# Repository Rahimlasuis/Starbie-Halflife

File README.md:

<h1>Starbie</h1>
<h2>Description</h2>
This is my very first hardware project.
i followed the starbie guide on halflife.
building some kind of desktop companion with some personal additional functions
<h2>Some of the processes</h2>
i started by bringing in components , symbols and power symbols in the schematic.
then i wired them up according to the guide.
i updated the pcb
traced the edges
routed the pcb
run DHR
ignored the errors,
I already fixed all the errors after my first rejection on halflife lol.
added some components of my own
opened arduino ide
installed all the things i was askd to install by the guide.
pasted the code
edited the code to work with my components
troublshooted
cried
tears
compiling errors, so many times, i think due to repeated lines of the same code
it finally wokrked

google was my friend all the way.
and it also gave me lot of work.
never let AI write codes for you.

I also suffered a lot because of my system. It was so slow and at some point i lost unsaved changes. I cried lol

here are some images too

<h2>Final Image</h2>

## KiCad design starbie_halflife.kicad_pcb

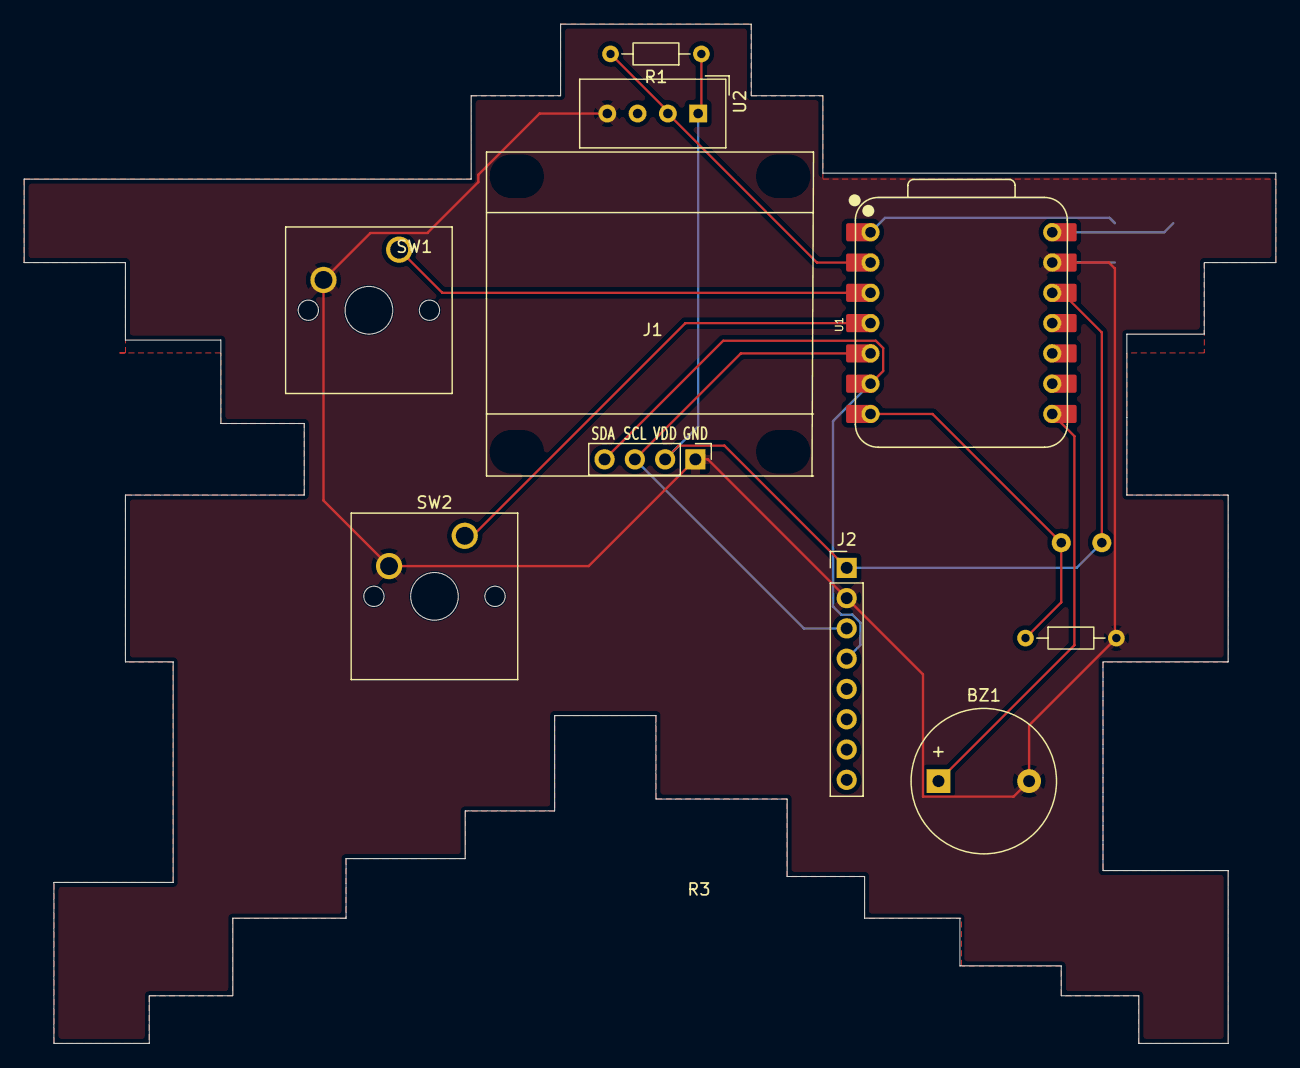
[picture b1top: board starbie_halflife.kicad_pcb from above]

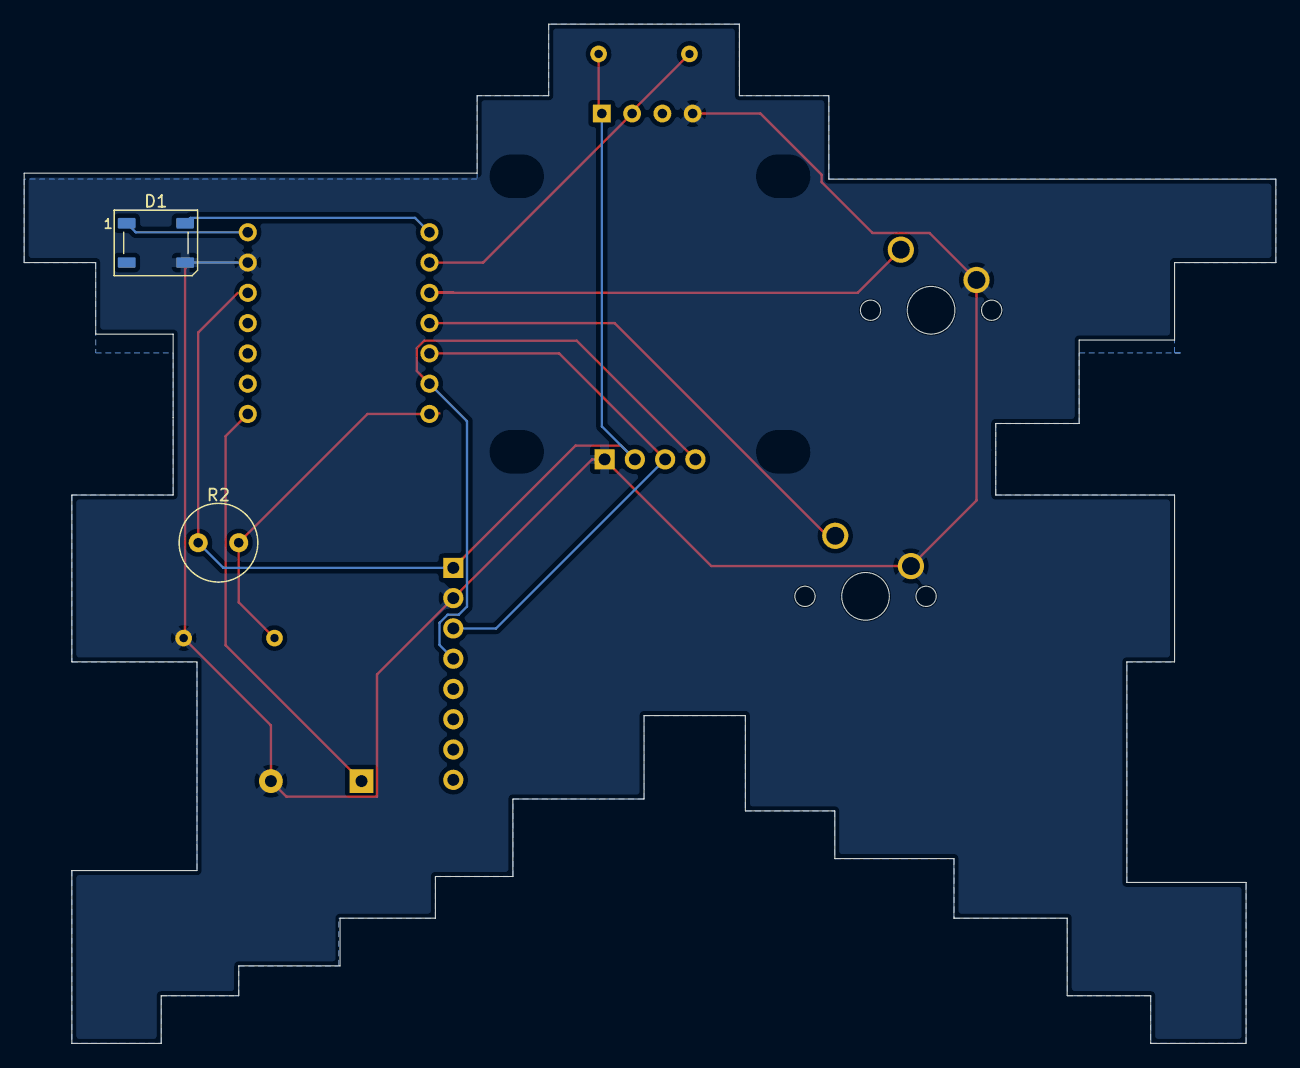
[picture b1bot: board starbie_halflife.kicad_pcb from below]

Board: 2 copper layers, 105.0 x 85.5 mm, 11 parts (2 on the bottom side), 11 nets.

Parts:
BZ1: Buzzer; Buzzer_12x9.5RM7.6
D1: WS2812B; LED_WS2812B_PLCC4_5.0x5.0mm_P3.2mm
J1: Conn_01x04_Pin; Display_128x64_096_I2C
J2: Conn_01x08_Pin; PinHeader_1x08_P2.54mm_Vertical
R1, R3: R; R_Axial_DIN0204_L3.6mm_D1.6mm_P7.62mm_Horizontal
R2: A1050; R_LDR_D6.4mm_P3.4mm_Vertical
SW1, SW2: SW_Push; SW_Cherry_MX_1.00u_PCB
U1: XIAO-ESP32-C3-SMD; XIAO-ESP32-C6-DIP
U2: DHT11; Aosong_DHT11_5.5x12.0_P2.54mm

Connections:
+3.3V: J1.2, J2.1, R1.1, R2.1, U1.12 (3V3_OUT), U2.1 (VDD)
+5V: D1.1 (VDD), U1.14 (VBUS)
/DHT11 DATA: R1.2, U1.2 (D1), U2.2 (DATA)
/GPIO2: SW1.1, U1.3 (D2)
/GPIO3: SW2.1, U1.4 (D3)
/SCL: J1.3, J2.3, U1.5 (D4)
/SDA: J1.4, J2.4, U1.6 (D5)
GND: BZ1.2 (-), D1.3 (VSS), J1.1, J2.2, R3.2, SW1.2, SW2.2, U1.13 (GND), U2.4 (GND)
unnamed: BZ1.1 (+), U1.8 (D7)
unnamed: D1.4 (DIN), U1.1 (D0)
unnamed: R2.2, R3.1, U1.7 (D6)

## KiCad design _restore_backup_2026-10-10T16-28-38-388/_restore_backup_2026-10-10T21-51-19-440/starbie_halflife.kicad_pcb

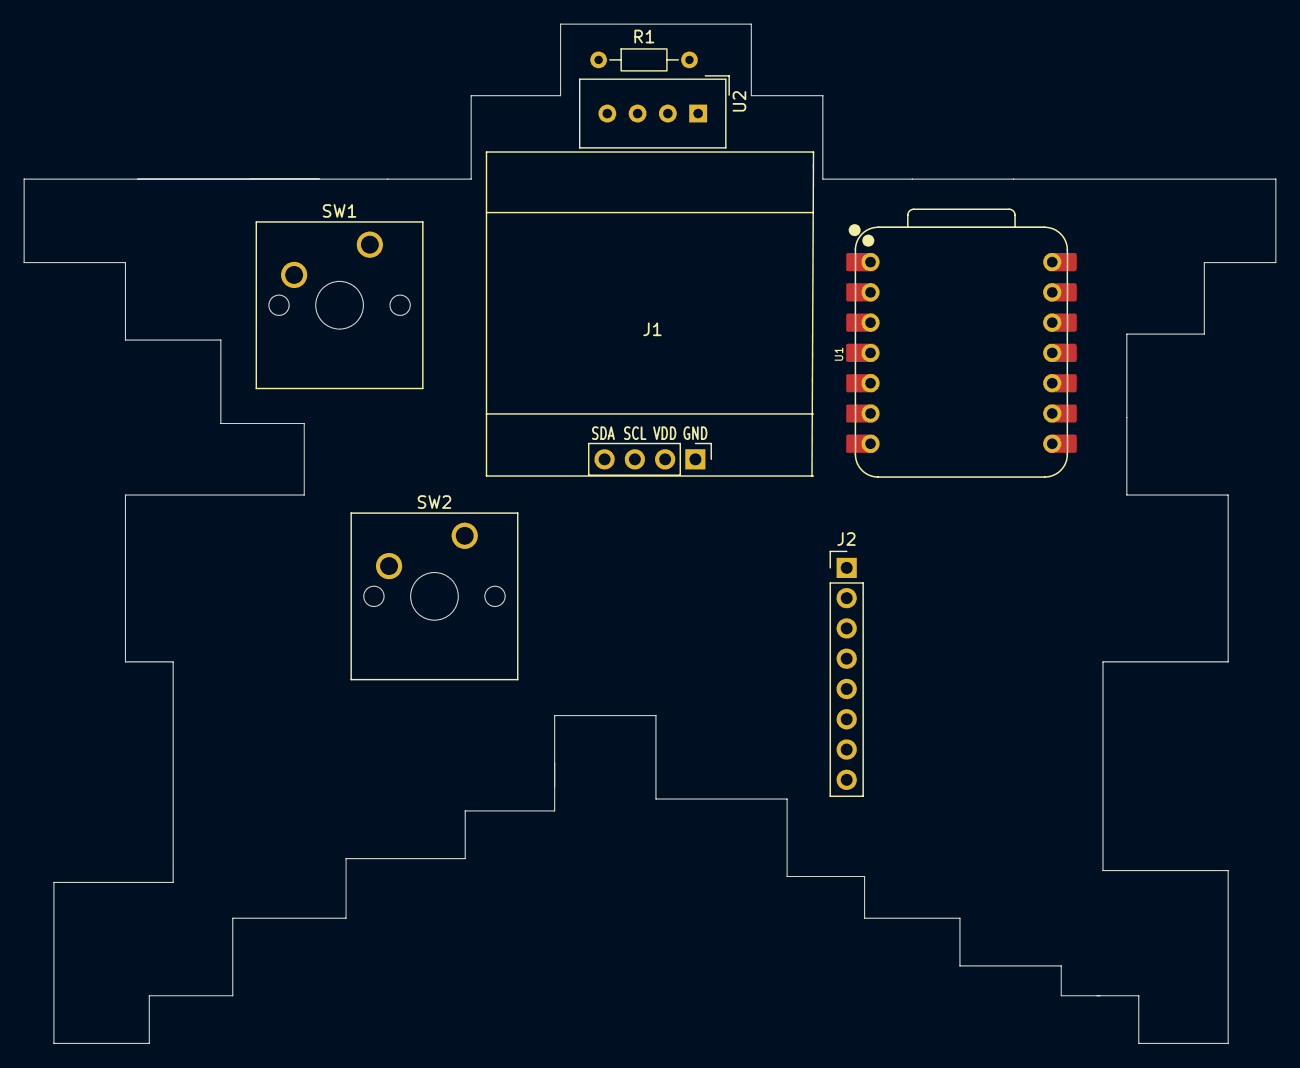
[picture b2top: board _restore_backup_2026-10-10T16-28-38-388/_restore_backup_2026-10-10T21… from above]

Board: 2 copper layers, 105.0 x 85.5 mm, 7 parts (0 on the bottom side), 2 nets, no tracks yet.

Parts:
J1: Conn_01x04_Pin; Display_128x64_096_I2C
J2: Conn_01x08_Pin; PinHeader_1x08_P2.54mm_Vertical
R1: R; R_Axial_DIN0204_L3.6mm_D1.6mm_P7.62mm_Horizontal
SW1, SW2: SW_Push; SW_Cherry_MX_1.00u_PCB
U1: XIAO-ESP32-C3-SMD; XIAO-ESP32-C6-DIP
U2: DHT11; Aosong_DHT11_5.5x12.0_P2.54mm

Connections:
+3.3V: J1.2, J2.1, R1.1, U1.12 (3V3_OUT), U2.1 (VDD)
GND: J1.1, J2.2, SW1.2, SW2.2, U1.13 (GND), U2.4 (GND)
